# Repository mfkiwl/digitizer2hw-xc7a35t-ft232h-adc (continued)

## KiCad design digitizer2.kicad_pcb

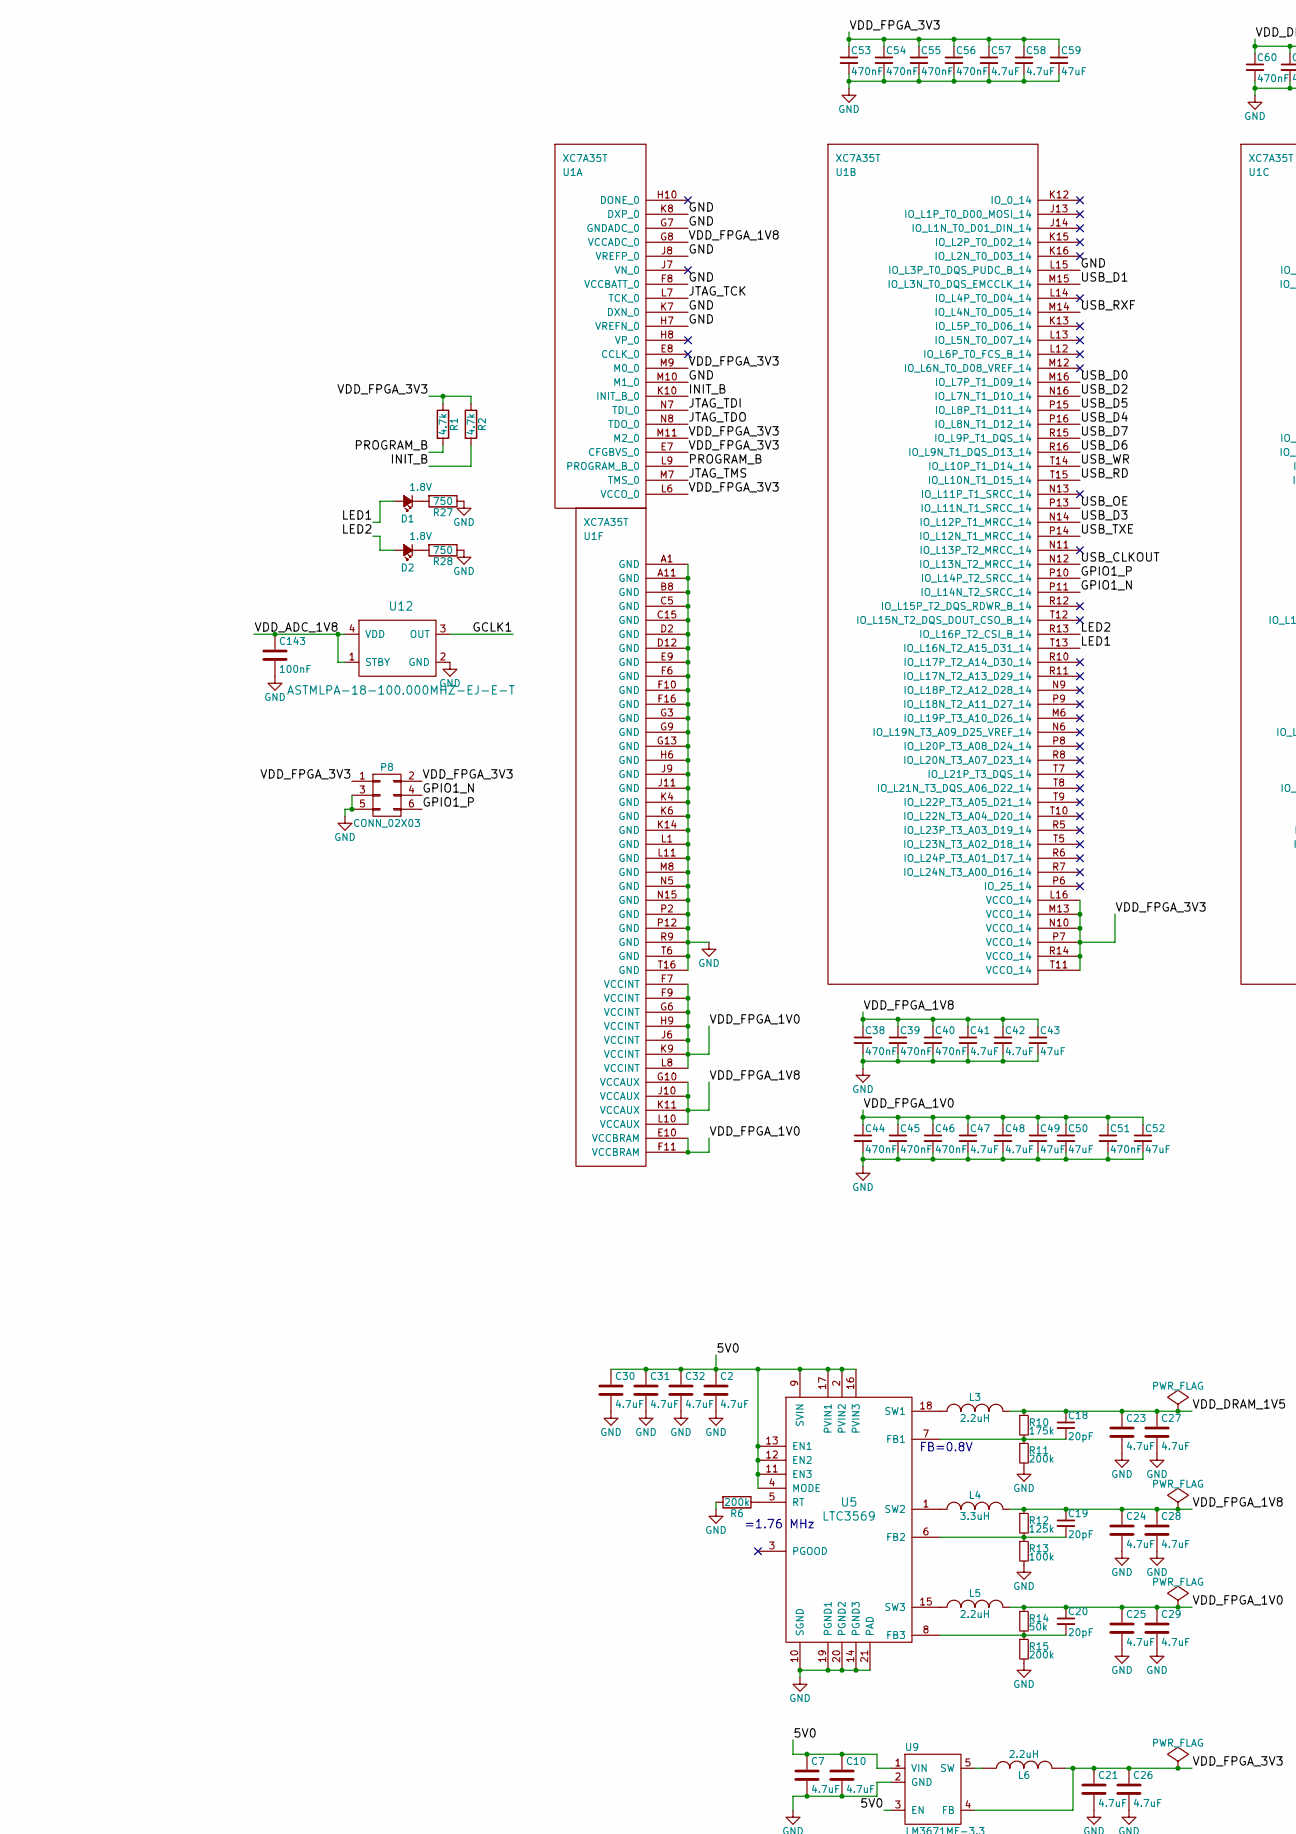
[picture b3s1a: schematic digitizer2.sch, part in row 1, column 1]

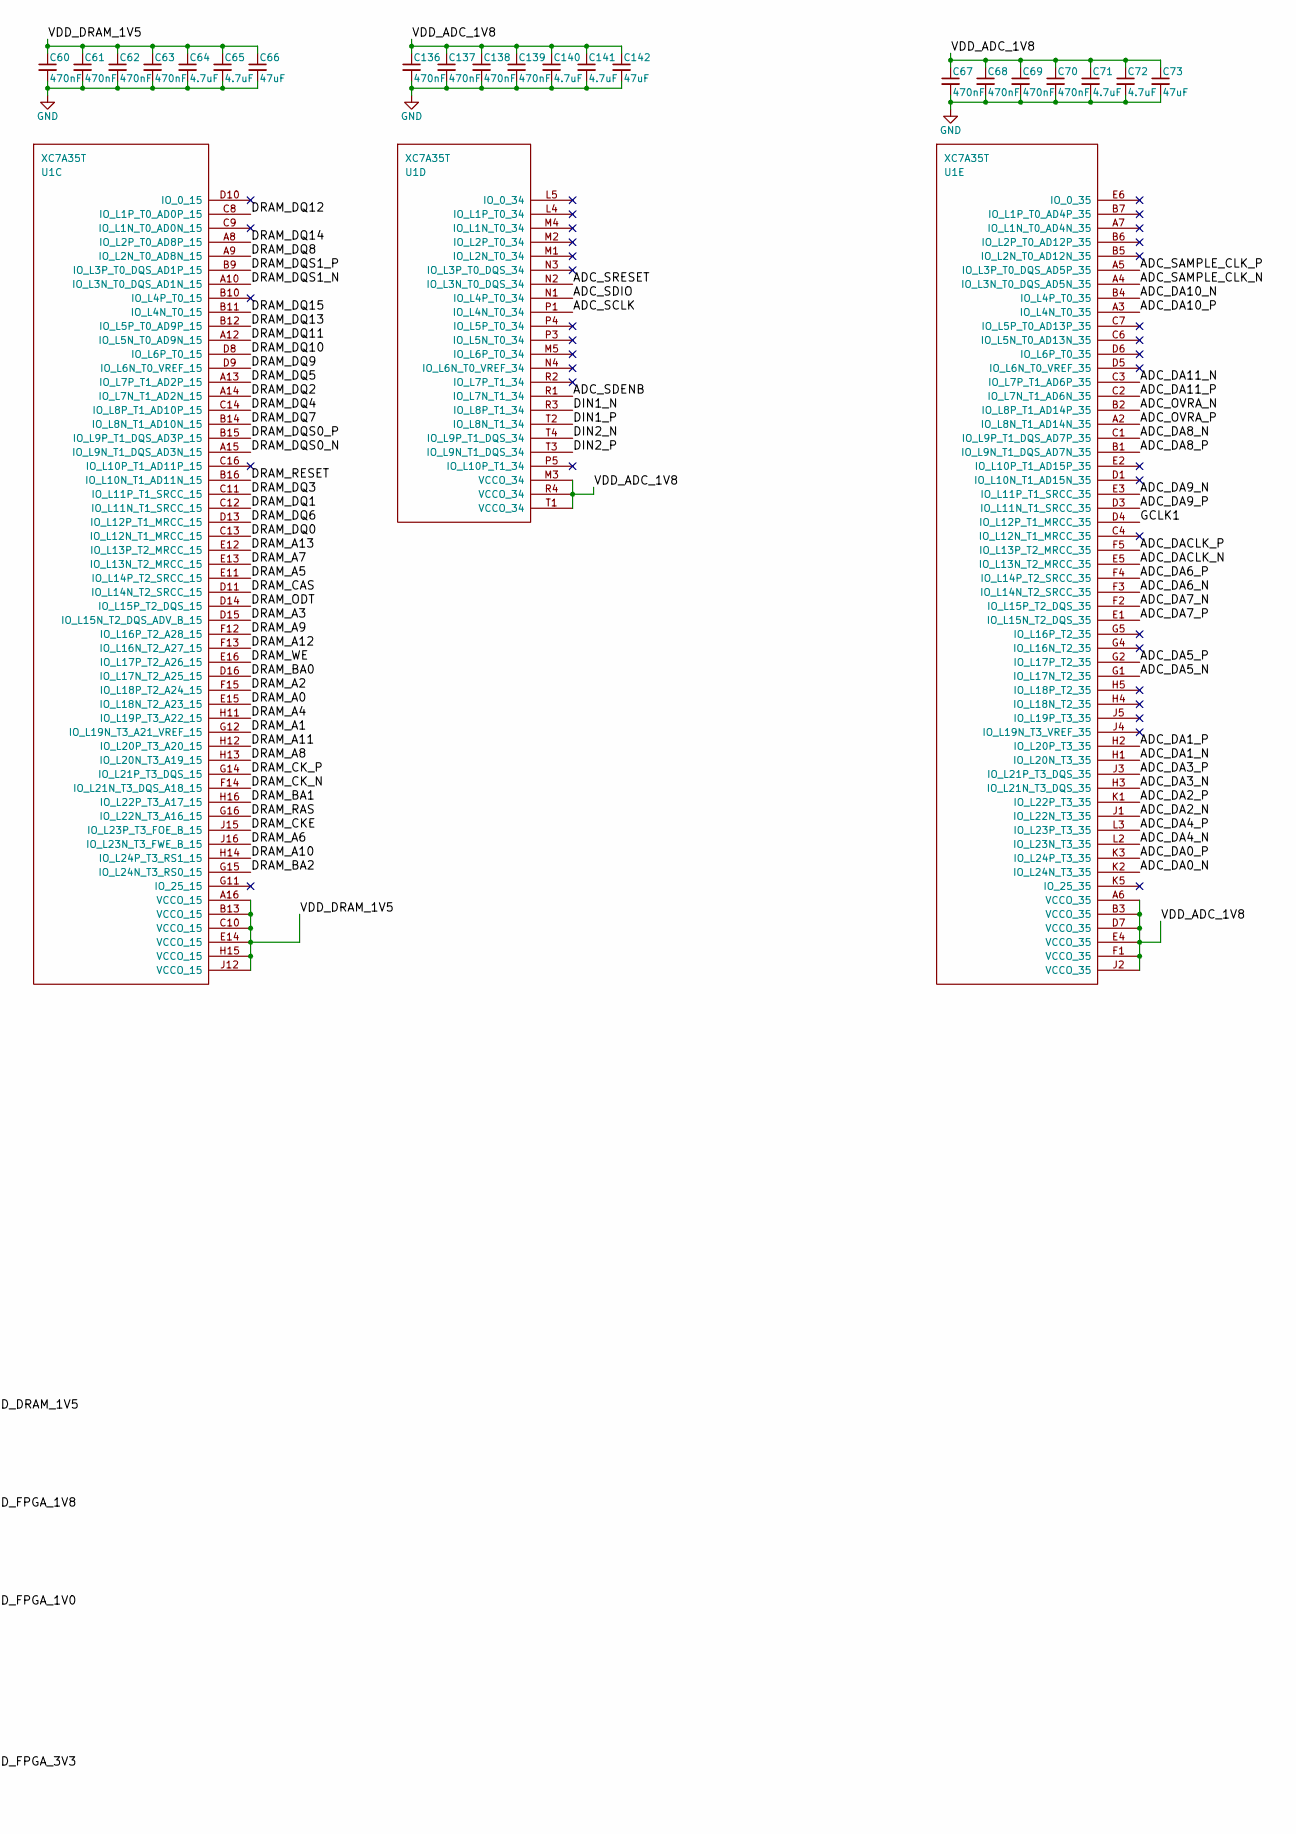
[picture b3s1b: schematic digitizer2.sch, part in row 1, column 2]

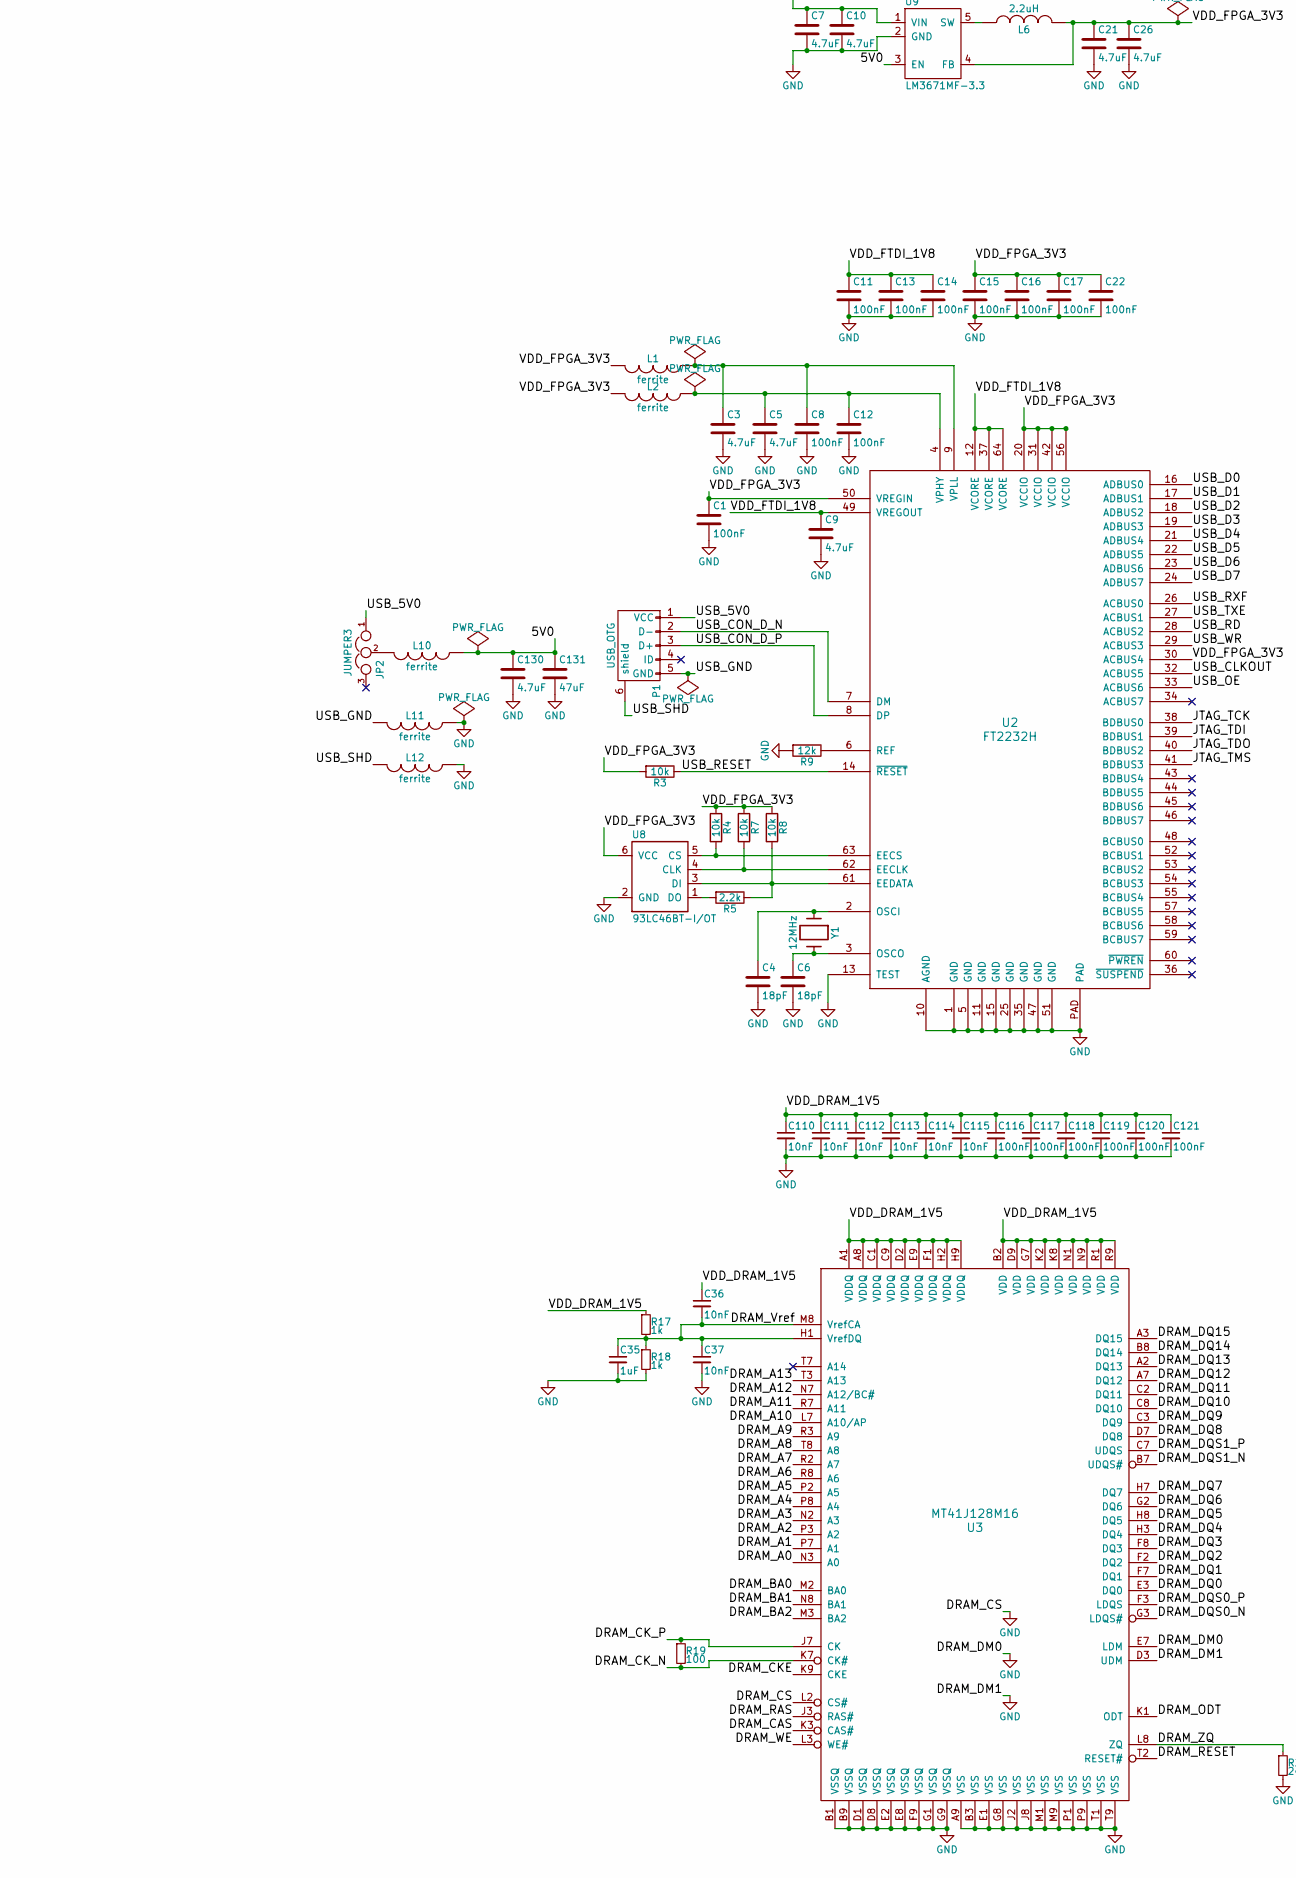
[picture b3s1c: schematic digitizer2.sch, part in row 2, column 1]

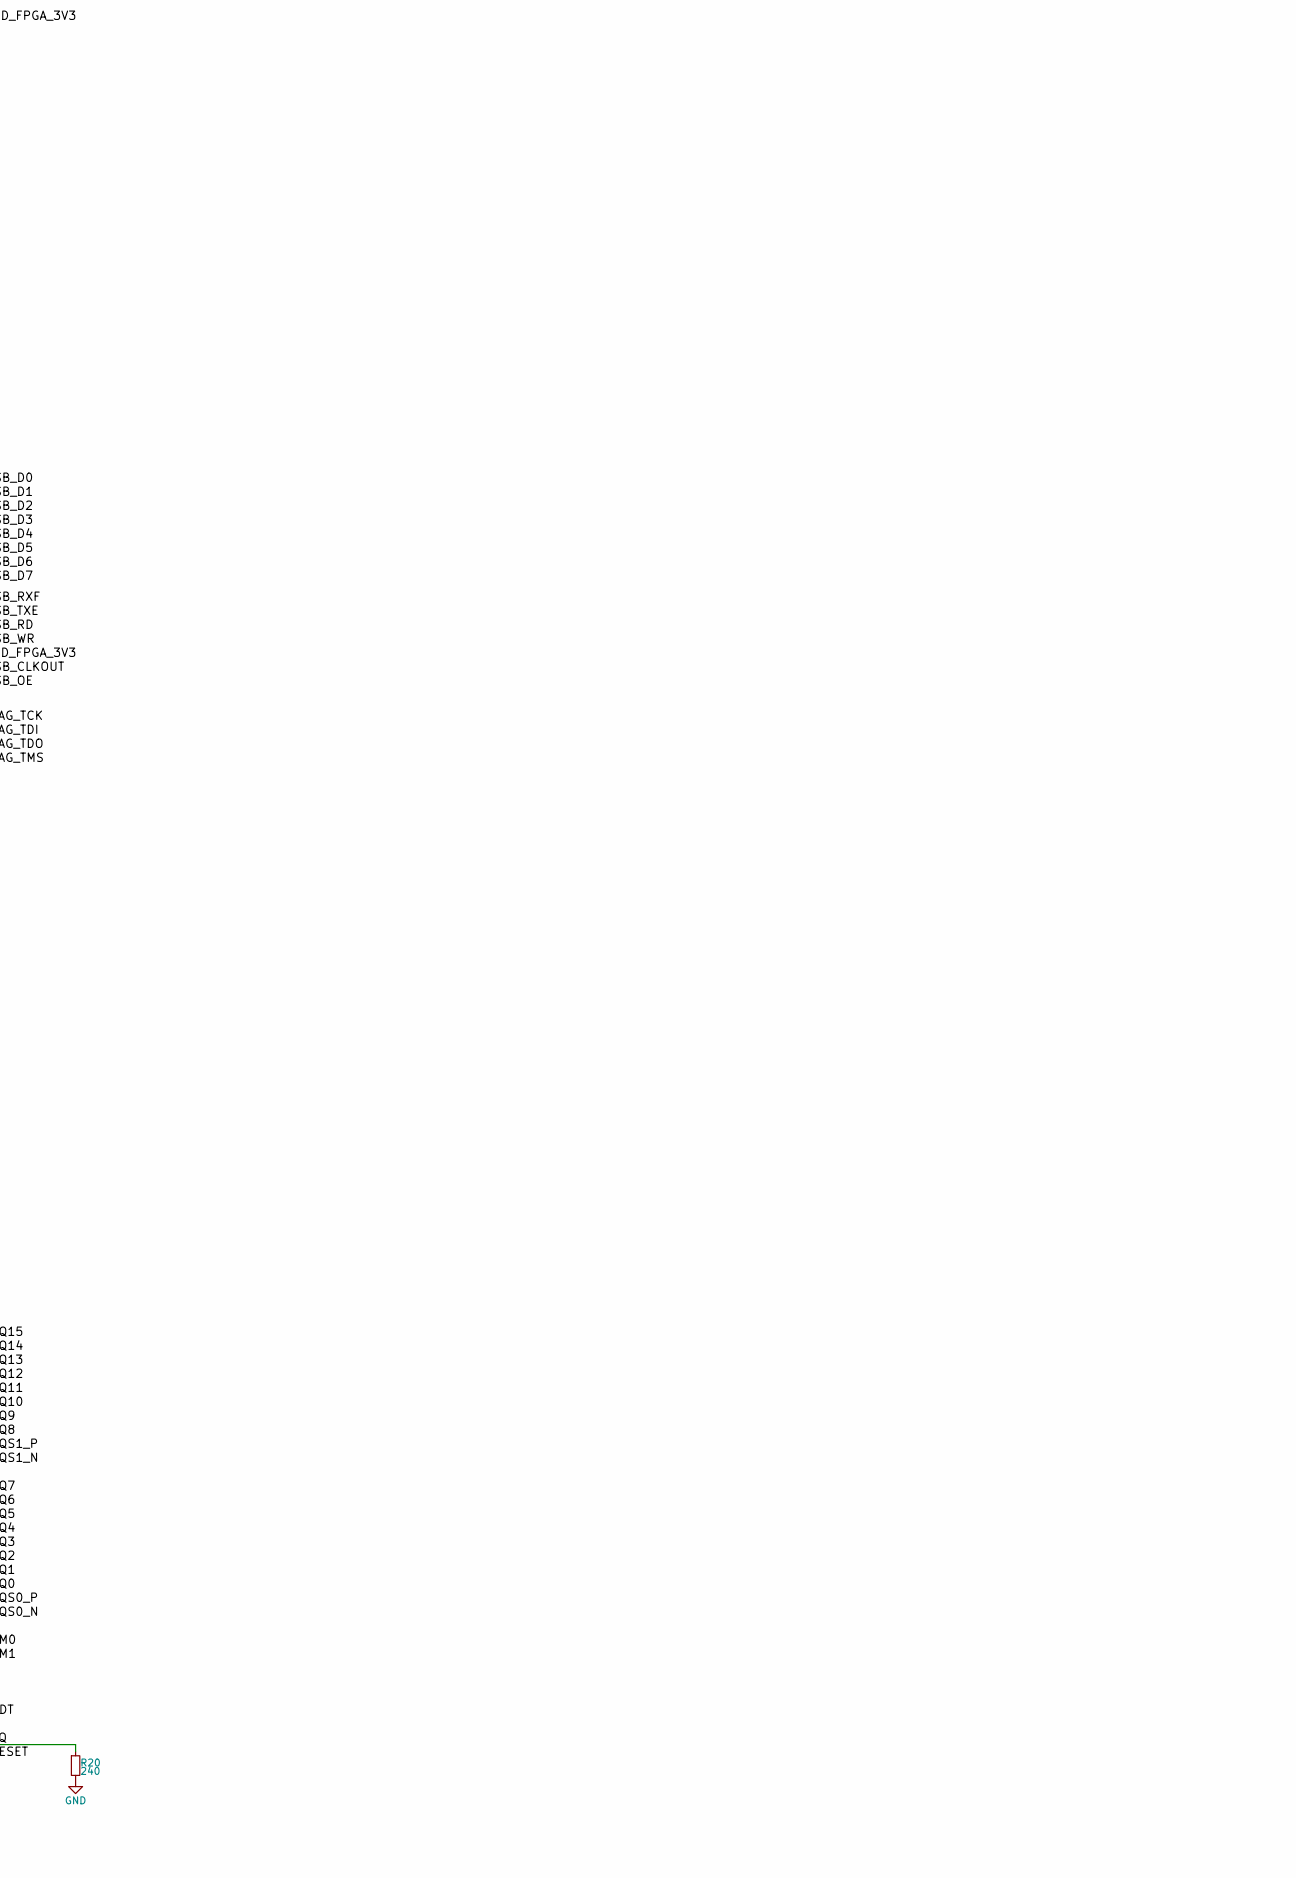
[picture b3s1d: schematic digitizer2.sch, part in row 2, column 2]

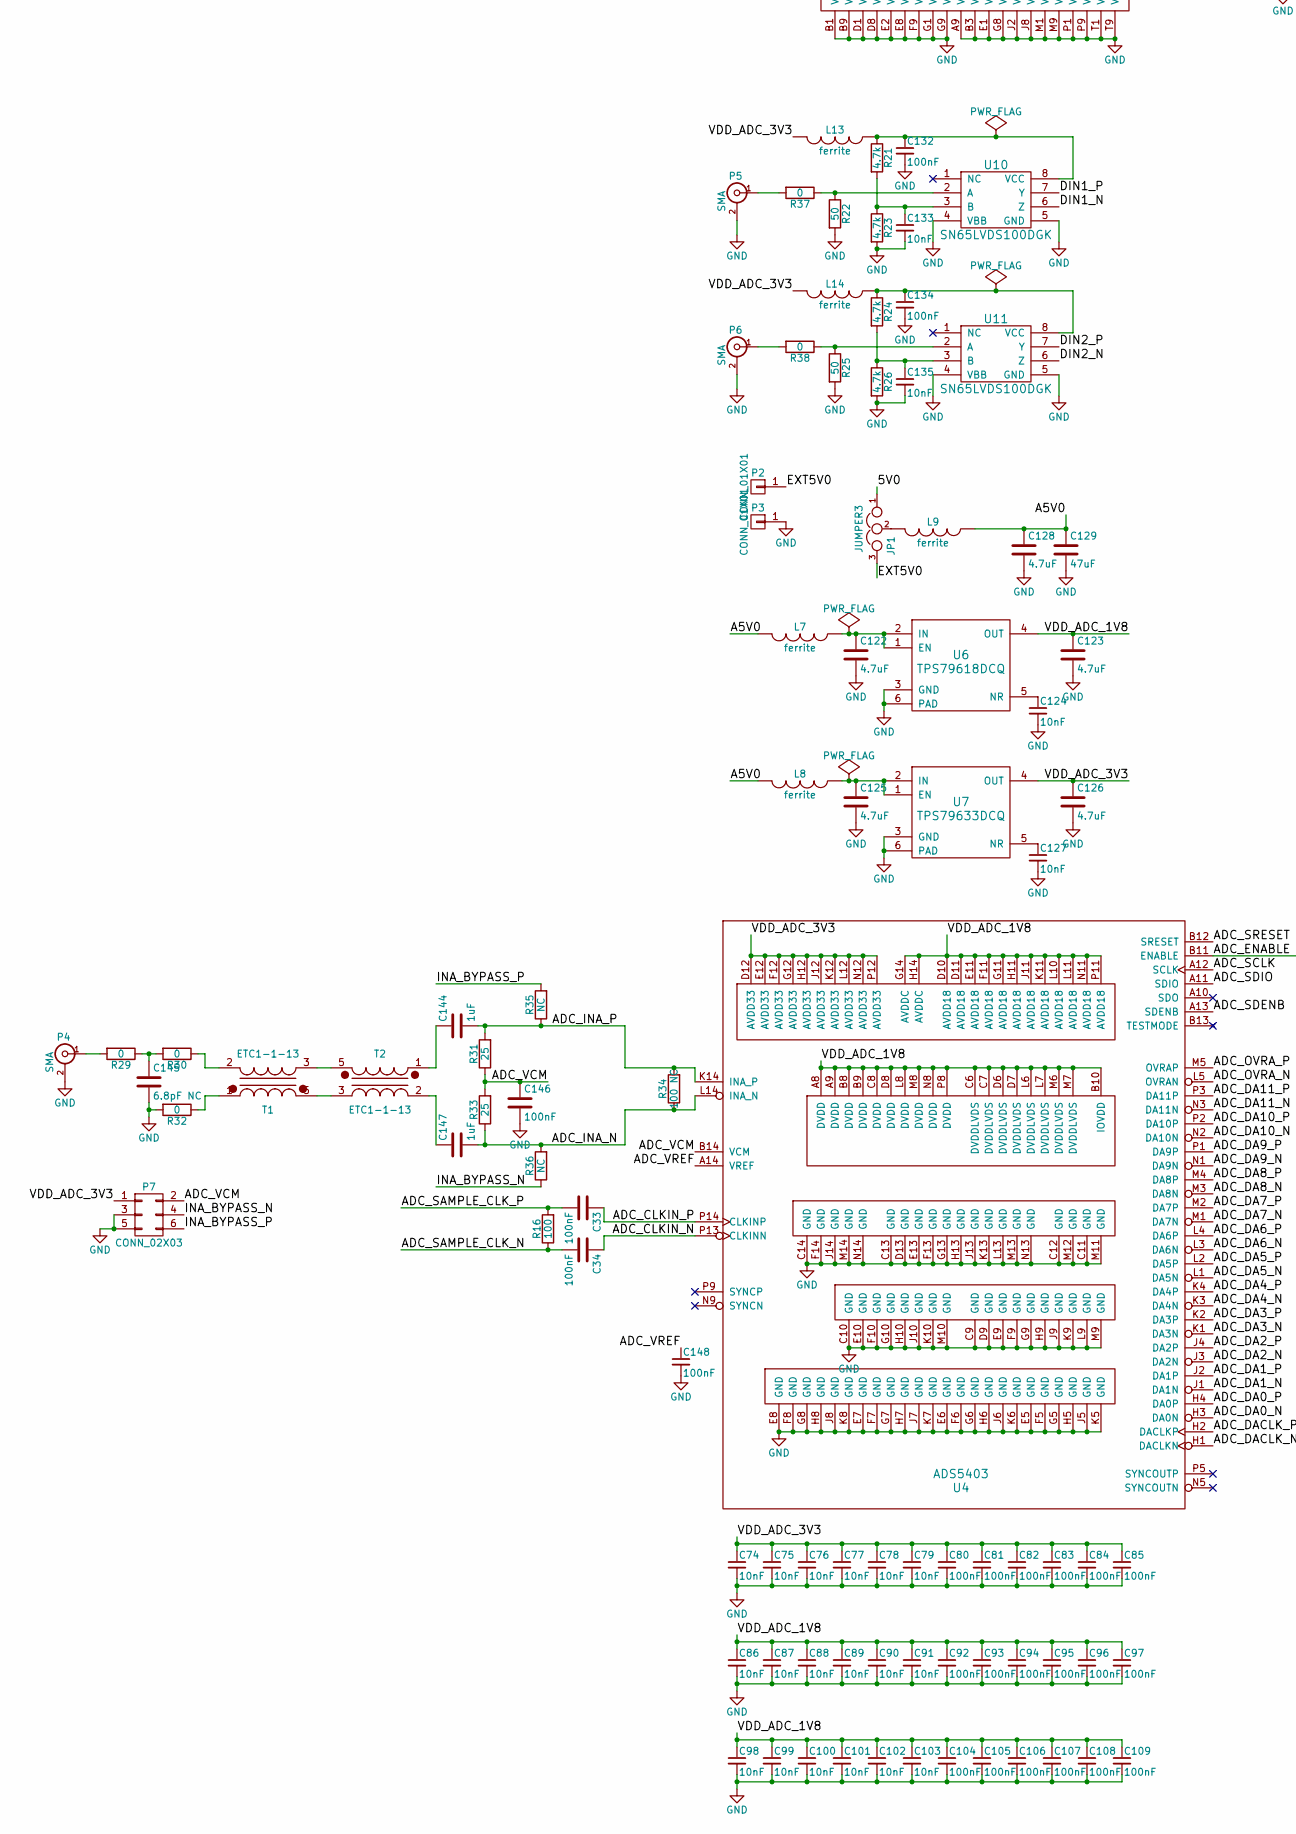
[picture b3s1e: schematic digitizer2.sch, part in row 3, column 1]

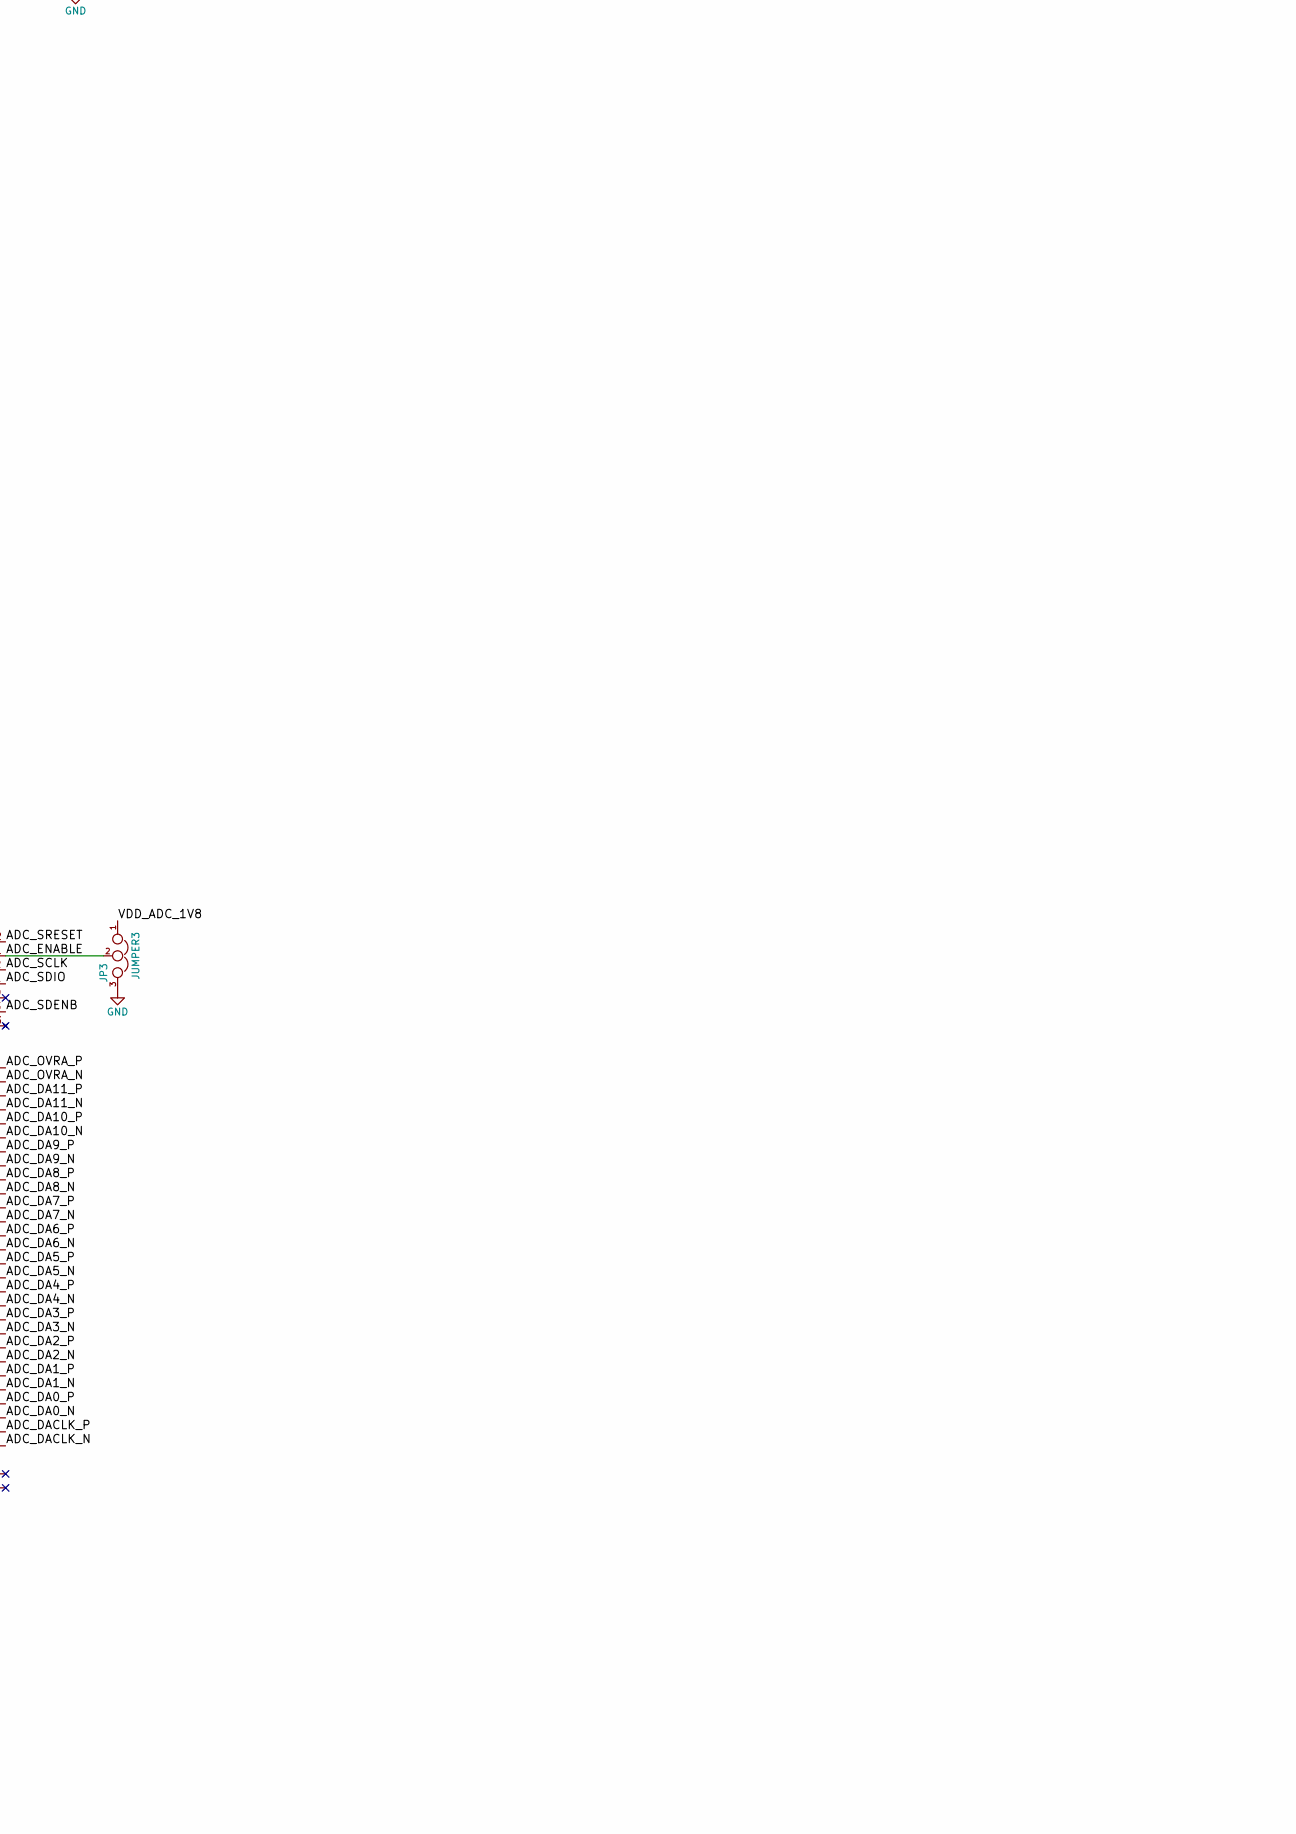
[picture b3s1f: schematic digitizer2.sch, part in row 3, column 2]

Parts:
C1, C8, C11, C12, C13, C14, C15, C16, C17, C22, C33, C34, C80, C81, C82, C83, C84, C85, C92, C93, C94, C95, C96, C97, C104, C105, C106, C107, C108, C109, C116, C117, C118, C119, C120, C121, C132, C134, C143, C146, C148: 100nF; C_0402
C2, C3, C5, C7, C9, C10, C21, C23, C24, C25, C26, C27, C28, C29, C30, C31, C32, C41, C42, C47, C48, C57, C58, C64, C65, C71, C72, C122, C123, C125, C126, C128, C130, C140, C141: 4.7uF; C_0402
C4, C6: 18pF; C_0603
C18, C19, C20: 20pF; C_0603
C35, C144, C147: 1uF; C_0402
C36, C37, C74, C75, C76, C77, C78, C79, C86, C87, C88, C89, C90, C91, C98, C99, C100, C101, C102, C103, C110, C111, C112, C113, C114, C115, C124, C127, C133, C135: 10nF; C_0402
C38, C39, C40, C44, C45, C46, C51, C53, C54, C55, C56, C60, C61, C62, C63, C67, C68, C69, C70, C136, C137, C138, C139: 470nF; C_0402
C43, C49, C50, C52, C59, C66, C73, C129, C131, C142: 47uF; C_0402
C145: 6.8pF NC; C_0603
D1, D2: 1.8V; LED_0603
JP1, JP2, JP3: JUMPER3; Pin_Header_Straight_1x03
L1, L2, L7, L8, L9, L10, L11, L12, L13, L14: ferrite; R_0805
L3, L5, L6: 2.2uH; IHLP-1212BZ-11
L4: 3.3uH; IHLP-1212BZ-11
P1: USB_OTG; USB_Micro-B
P2, P3: CONN_01X01; Banana_Jack_1Pin
P4, P5, P6: SMA; SMA_ANGLE_THT
P7, P8: CONN_02X03; Pin_Header_Angled_2x03
R1, R2, R21, R23, R24, R26: 4.7k; R_0402
R3, R4, R7, R8: 10k; R_0603
R5: 2.2k; R_0603
R6, R11, R15: 200k; R_0603
R9: 12k; R_0603
R10: 175k; R_0603
R12: 125k; R_0603
R13: 100k; R_0603
R14: 50k; R_0603
R16, R19: 100; R_0402
R17, R18: 1k; R_0402
R20: 240; R_0402
R22, R25: 50; R_0402
R27, R28: 750; R_0603
R29, R30, R32: 0; R_0603
R31, R33: 25; R_0402
R34: 100 NC; R_0402
R35, R36: NC; R_0402
R37, R38: 0; R_0402
T1, T2: ETC1-1-13
U1: XC7A35T; BGA-256_pitch1mm_dia0.4mm
U2: FT2232H; QFN-FT2232HQ-64_pitch0.5
U3: MT41J128M16; BGA-96_pitch0.8mm_dia0.35mm
U4: ADS5403; BGA-196_pitch0.8mm_dia0.4mm
U5: LTC3569; UQFN-20-1EP_3x3mm_Pitch0.4mm
U6: TPS79618DCQ; SOT-223-6
U7: TPS79633DCQ; SOT-223-6
U8: 93LC46BT-I/OT; SOT-23-6
U9: LM3671MF-3.3; SOT-23-6
U10, U11: SN65LVDS100DGK; TSSOP-8_3x3mm_Pitch0.65mm
U12: ASTMLPA-18-100.000MHZ-EJ-E-T; ASTMLPA
Y1: 12MHz; Crystal_SMD_5032_2Pads

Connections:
/5V0: C2.1, C7.1, C10.1, C30.1, C31.1, C32.1, C130.1, C131.1, JP1.1, L10.1, U5.2 (PVIN2), U5.4 (MODE), U5.9 (SVIN), U5.11 (EN3), U5.12 (EN2), U5.13 (EN1), U5.16 (PVIN3), U5.17 (PVIN1), U9.1 (VIN), U9.3 (EN)
/A5V0: C128.1, C129.1, L7.2, L8.2, L9.1
/ADC_CLKIN_N: C34.1, U4.P13 (CLKINN)
/ADC_CLKIN_P: C33.1, U4.P14 (CLKINP)
/ADC_DA0_N: U1.K2 (IO_L24N_T3_35), U4.H3 (DA0N)
/ADC_DA0_P: U1.K3 (IO_L24P_T3_35), U4.H4 (DA0P)
/ADC_DA1_N: U1.H1 (IO_L20N_T3_35), U4.J1 (DA1N)
/ADC_DA1_P: U1.H2 (IO_L20P_T3_35), U4.J2 (DA1P)
/ADC_DA2_N: U1.J1 (IO_L22N_T3_35), U4.J3 (DA2N)
/ADC_DA2_P: U1.K1 (IO_L22P_T3_35), U4.J4 (DA2P)
/ADC_DA3_N: U1.H3 (IO_L21N_T3_DQS_35), U4.K1 (DA3N)
/ADC_DA3_P: U1.J3 (IO_L21P_T3_DQS_35), U4.K2 (DA3P)
/ADC_DA4_N: U1.L2 (IO_L23N_T3_35), U4.K3 (DA4N)
/ADC_DA4_P: U1.L3 (IO_L23P_T3_35), U4.K4 (DA4P)
/ADC_DA5_N: U1.G1 (IO_L17N_T2_35), U4.L1 (DA5N)
/ADC_DA5_P: U1.G2 (IO_L17P_T2_35), U4.L2 (DA5P)
/ADC_DA6_N: U1.F3 (IO_L14N_T2_SRCC_35), U4.L3 (DA6N)
/ADC_DA6_P: U1.F4 (IO_L14P_T2_SRCC_35), U4.L4 (DA6P)
/ADC_DA7_N: U1.F2 (IO_L15P_T2_DQS_35), U4.M1 (DA7N)
/ADC_DA7_P: U1.E1 (IO_L15N_T2_DQS_35), U4.M2 (DA7P)
/ADC_DA8_N: U1.C1 (IO_L9P_T1_DQS_AD7P_35), U4.M3 (DA8N)
/ADC_DA8_P: U1.B1 (IO_L9N_T1_DQS_AD7N_35), U4.M4 (DA8P)
/ADC_DA9_N: U1.E3 (IO_L11P_T1_SRCC_35), U4.N1 (DA9N)
/ADC_DA9_P: U1.D3 (IO_L11N_T1_SRCC_35), U4.P1 (DA9P)
/ADC_DA10_N: U1.B4 (IO_L4P_T0_35), U4.N2 (DA10N)
/ADC_DA10_P: U1.A3 (IO_L4N_T0_35), U4.P2 (DA10P)
/ADC_DA11_N: U1.C3 (IO_L7P_T1_AD6P_35), U4.N3 (DA11N)
/ADC_DA11_P: U1.C2 (IO_L7N_T1_AD6N_35), U4.P3 (DA11P)
/ADC_DACLK_N: U1.E5 (IO_L13N_T2_MRCC_35), U4.H1 (DACLKN)
/ADC_DACLK_P: U1.F5 (IO_L13P_T2_MRCC_35), U4.H2 (DACLKP)
/ADC_ENABLE: JP3.2, U4.B11 (ENABLE)
/ADC_INA_N: C147.2, R33.1, R34.1, R36.2, U4.L14 (INA_N)
/ADC_INA_P: C144.2, R31.2, R34.2, R35.1, U4.K14 (INA_P)
/ADC_OVRA_N: U1.B2 (IO_L8P_T1_AD14P_35), U4.L5 (OVRAN)
/ADC_OVRA_P: U1.A2 (IO_L8N_T1_AD14N_35), U4.M5 (OVRAP)
/ADC_SAMPLE_CLK_N: C34.2, R16.1, U1.A4 (IO_L3N_T0_DQS_AD5N_35)
/ADC_SAMPLE_CLK_P: C33.2, R16.2, U1.A5 (IO_L3P_T0_DQS_AD5P_35)
/ADC_SCLK: U1.P1 (IO_L4N_T0_34), U4.A12 (SCLK)
/ADC_SDENB: U1.R1 (IO_L7N_T1_34), U4.A13 (SDENB)
/ADC_SDIO: U1.N1 (IO_L4P_T0_34), U4.A11 (SDIO)
/ADC_SRESET: U1.N2 (IO_L3N_T0_DQS_34), U4.B12 (SRESET)
/ADC_VCM: C146.1, P7.2, R31.1, R33.2, U4.B14 (VCM)
/ADC_VREF: C148.1, U4.A14 (VREF)
/DIN1_N: U1.R3 (IO_L8P_T1_34), U10.6 (Z)
/DIN1_P: U1.T2 (IO_L8N_T1_34), U10.7 (Y)
/DIN2_N: U1.T4 (IO_L9P_T1_DQS_34), U11.6 (Z)
/DIN2_P: U1.T3 (IO_L9N_T1_DQS_34), U11.7 (Y)
/DRAM_A0: U1.E15 (IO_L18N_T2_A23_15), U3.N3 (A0)
/DRAM_A1: U1.G12 (IO_L19N_T3_A21_VREF_15), U3.P7 (A1)
/DRAM_A2: U1.F15 (IO_L18P_T2_A24_15), U3.P3 (A2)
/DRAM_A3: U1.D15 (IO_L15N_T2_DQS_ADV_B_15), U3.N2 (A3)
/DRAM_A4: U1.H11 (IO_L19P_T3_A22_15), U3.P8 (A4)
/DRAM_A5: U1.E11 (IO_L14P_T2_SRCC_15), U3.P2 (A5)
/DRAM_A6: U1.J16 (IO_L23N_T3_FWE_B_15), U3.R8 (A6)
/DRAM_A7: U1.E13 (IO_L13N_T2_MRCC_15), U3.R2 (A7)
/DRAM_A8: U1.H13 (IO_L20N_T3_A19_15), U3.T8 (A8)
/DRAM_A9: U1.F12 (IO_L16P_T2_A28_15), U3.R3 (A9)
/DRAM_A10: U1.H14 (IO_L24P_T3_RS1_15), U3.L7 (A10/AP)
/DRAM_A11: U1.H12 (IO_L20P_T3_A20_15), U3.R7 (A11)
/DRAM_A12: U1.F13 (IO_L16N_T2_A27_15), U3.N7 (A12/BC#)
/DRAM_A13: U1.E12 (IO_L13P_T2_MRCC_15), U3.T3 (A13)
/DRAM_BA0: U1.D16 (IO_L17N_T2_A25_15), U3.M2 (BA0)
/DRAM_BA1: U1.H16 (IO_L22P_T3_A17_15), U3.N8 (BA1)
/DRAM_BA2: U1.G15 (IO_L24N_T3_RS0_15), U3.M3 (BA2)
/DRAM_CAS: U1.D11 (IO_L14N_T2_SRCC_15), U3.K3 (CAS#)
/DRAM_CKE: U1.J15 (IO_L23P_T3_FOE_B_15), U3.K9 (CKE)
/DRAM_CK_N: R19.2, U1.F14 (IO_L21N_T3_DQS_A18_15), U3.K7 (CK#)
/DRAM_CK_P: R19.1, U1.G14 (IO_L21P_T3_DQS_15), U3.J7 (CK)
/DRAM_DQ0: U1.C13 (IO_L12N_T1_MRCC_15), U3.E3 (DQ0)
/DRAM_DQ1: U1.C12 (IO_L11N_T1_SRCC_15), U3.F7 (DQ1)
/DRAM_DQ2: U1.A14 (IO_L7N_T1_AD2N_15), U3.F2 (DQ2)
/DRAM_DQ3: U1.C11 (IO_L11P_T1_SRCC_15), U3.F8 (DQ3)
/DRAM_DQ4: U1.C14 (IO_L8P_T1_AD10P_15), U3.H3 (DQ4)
/DRAM_DQ5: U1.A13 (IO_L7P_T1_AD2P_15), U3.H8 (DQ5)
/DRAM_DQ6: U1.D13 (IO_L12P_T1_MRCC_15), U3.G2 (DQ6)
/DRAM_DQ7: U1.B14 (IO_L8N_T1_AD10N_15), U3.H7 (DQ7)
/DRAM_DQ8: U1.A9 (IO_L2N_T0_AD8N_15), U3.D7 (DQ8)
/DRAM_DQ9: U1.D9 (IO_L6N_T0_VREF_15), U3.C3 (DQ9)
/DRAM_DQ10: U1.D8 (IO_L6P_T0_15), U3.C8 (DQ10)
/DRAM_DQ11: U1.A12 (IO_L5N_T0_AD9N_15), U3.C2 (DQ11)
/DRAM_DQ12: U1.C8 (IO_L1P_T0_AD0P_15), U3.A7 (DQ12)
/DRAM_DQ13: U1.B12 (IO_L5P_T0_AD9P_15), U3.A2 (DQ13)
/DRAM_DQ14: U1.A8 (IO_L2P_T0_AD8P_15), U3.B8 (DQ14)
/DRAM_DQ15: U1.B11 (IO_L4N_T0_15), U3.A3 (DQ15)
/DRAM_DQS0_N: U1.A15 (IO_L9N_T1_DQS_AD3N_15), U3.G3 (LDQS#)
/DRAM_DQS0_P: U1.B15 (IO_L9P_T1_DQS_AD3P_15), U3.F3 (LDQS)
/DRAM_DQS1_N: U1.A10 (IO_L3N_T0_DQS_AD1N_15), U3.B7 (UDQS#)
/DRAM_DQS1_P: U1.B9 (IO_L3P_T0_DQS_AD1P_15), U3.C7 (UDQS)
/DRAM_ODT: U1.D14 (IO_L15P_T2_DQS_15), U3.K1 (ODT)
/DRAM_RAS: U1.G16 (IO_L22N_T3_A16_15), U3.J3 (RAS#)
/DRAM_RESET: U1.B16 (IO_L10N_T1_AD11N_15), U3.T2 (RESET#)
/DRAM_Vref: C35.1, C36.2, C37.1, R17.2, R18.1, U3.H1 (VrefDQ), U3.M8 (VrefCA)
/DRAM_WE: U1.E16 (IO_L17P_T2_A26_15), U3.L3 (WE#)
/DRAM_ZQ: R20.1, U3.L8 (ZQ)
/EXT5V0: JP1.3, P2.1
/GCLK1: U1.D4 (IO_L12P_T1_MRCC_35), U12.3 (OUT)
/GPIO1_N: P8.4, U1.P11 (IO_L14N_T2_SRCC_14)
/GPIO1_P: P8.6, U1.P10 (IO_L14P_T2_SRCC_14)
/INA_BYPASS_N: P7.4, R36.1
/INA_BYPASS_P: P7.6, R35.2
/INIT_B: R2.2, U1.K10 (INIT_B_0)
/JTAG_TCK: U1.L7 (TCK_0), U2.38 (BDBUS0)
/JTAG_TDI: U1.N7 (TDI_0), U2.39 (BDBUS1)
/JTAG_TDO: U1.N8 (TDO_0), U2.40 (BDBUS2)
/JTAG_TMS: U1.M7 (TMS_0), U2.41 (BDBUS3)
/LED1: D1.2 (A), U1.T13 (IO_L16N_T2_A15_D31_14)
/LED2: D2.2 (A), U1.R13 (IO_L16P_T2_CSI_B_14)
/PROGRAM_B: R1.2, U1.L9 (PROGRAM_B_0)
/USB_5V0: JP2.1, P1.1 (VCC)
/USB_CLKOUT: U1.N12 (IO_L13N_T2_MRCC_14), U2.32 (ACBUS5)
/USB_CON_D_N: P1.2 (D-), U2.7 (DM)
/USB_CON_D_P: P1.3 (D+), U2.8 (DP)
/USB_D0: U1.M16 (IO_L7P_T1_D09_14), U2.16 (ADBUS0)
/USB_D1: U1.M15 (IO_L3N_T0_DQS_EMCCLK_14), U2.17 (ADBUS1)
/USB_D2: U1.N16 (IO_L7N_T1_D10_14), U2.18 (ADBUS2)
/USB_D3: U1.N14 (IO_L12P_T1_MRCC_14), U2.19 (ADBUS3)
/USB_D4: U1.P16 (IO_L8N_T1_D12_14), U2.21 (ADBUS4)
/USB_D5: U1.P15 (IO_L8P_T1_D11_14), U2.22 (ADBUS5)
/USB_D6: U1.R16 (IO_L9N_T1_DQS_D13_14), U2.23 (ADBUS6)
/USB_D7: U1.R15 (IO_L9P_T1_DQS_14), U2.24 (ADBUS7)
/USB_GND: L11.2, P1.5 (GND)
/USB_OE: U1.P13 (IO_L11N_T1_SRCC_14), U2.33 (ACBUS6)
/USB_RD: U1.T15 (IO_L10N_T1_D15_14), U2.28 (ACBUS2)
/USB_RESET: R3.1, U2.14 (~RESET)
/USB_RXF: U1.M14 (IO_L4N_T0_D05_14), U2.26 (ACBUS0)
/USB_SHD: L12.2, P1.6 (shield)
/USB_TXE: U1.P14 (IO_L12N_T1_MRCC_14), U2.27 (ACBUS1)
/USB_WR: U1.T14 (IO_L10P_T1_D14_14), U2.29 (ACBUS3)
/VDD_ADC_1V8: C67.1, C68.1, C69.1, C70.1, C71.1, C72.1, C73.1, C86.1, C87.1, C88.1, C89.1, C90.1, C91.1, C92.1, C93.1, C94.1, C95.1, C96.1, C97.1, C98.1, C99.1, C100.1, C101.1, C102.1, C103.1, C104.1, C105.1, C106.1, C107.1, C108.1, C109.1, C123.1, C136.1, C137.1, C138.1, C139.1, C140.1, C141.1, C142.1, C143.1, JP3.1, U1.A6 (VCCO_35), U1.B3 (VCCO_35), U1.D7 (VCCO_35), U1.E4 (VCCO_35), U1.F1 (VCCO_35), U1.J2 (VCCO_35), U1.M3 (VCCO_34), U1.R4 (VCCO_34), U1.T1 (VCCO_34), U4.A8 (DVDD), U4.A9 (DVDD), U4.B8 (DVDD), U4.B9 (DVDD), U4.B10 (IOVDD), U4.C6 (DVDDLVDS), U4.C7 (DVDDLVDS), U4.C8 (DVDD), U4.D6 (DVDDLVDS), U4.D7 (DVDDLVDS), U4.D8 (DVDD), U4.D10 (AVDD18), U4.D11 (AVDD18), U4.E11 (AVDD18), U4.F11 (AVDD18), U4.G11 (AVDD18), U4.G14 (AVDDC), U4.H11 (AVDD18), U4.H14 (AVDDC), U4.J11 (AVDD18), U4.K11 (AVDD18), U4.L6 (DVDDLVDS), U4.L7 (DVDDLVDS), U4.L8 (DVDD), U4.L10 (AVDD18), U4.L11 (AVDD18), U4.M6 (DVDDLVDS), U4.M7 (DVDDLVDS), U4.M8 (DVDD), U4.N8 (DVDD), U4.N11 (AVDD18), U4.P8 (DVDD), U4.P11 (AVDD18), U6.4 (OUT), U12.1 (STBY), U12.4 (VDD)
/VDD_ADC_3V3: C74.1, C75.1, C76.1, C77.1, C78.1, C79.1, C80.1, C81.1, C82.1, C83.1, C84.1, C85.1, C126.1, L13.2, L14.2, P7.1, U4.D12 (AVDD33), U4.E12 (AVDD33), U4.F12 (AVDD33), U4.G12 (AVDD33), U4.H12 (AVDD33), U4.J12 (AVDD33), U4.K12 (AVDD33), U4.L12 (AVDD33), U4.N12 (AVDD33), U4.P12 (AVDD33), U7.4 (OUT)
/VDD_DRAM_1V5: C18.1, C23.1, C27.1, C36.1, C60.1, C61.1, C62.1, C63.1, C64.1, C65.1, C66.1, C110.1, C111.1, C112.1, C113.1, C114.1, C115.1, C116.1, C117.1, C118.1, C119.1, C120.1, C121.1, L3.2, R10.1, R17.1, U1.A16 (VCCO_15), U1.B13 (VCCO_15), U1.C10 (VCCO_15), U1.E14 (VCCO_15), U1.H15 (VCCO_15), U1.J12 (VCCO_15), U3.A1 (VDDQ), U3.A8 (VDDQ), U3.B2 (VDD), U3.C1 (VDDQ), U3.C9 (VDDQ), U3.D2 (VDDQ), U3.D9 (VDD), U3.E9 (VDDQ), U3.F1 (VDDQ), U3.G7 (VDD), U3.H2 (VDDQ), U3.H9 (VDDQ), U3.K2 (VDD), U3.K8 (VDD), U3.N1 (VDD), U3.N9 (VDD), U3.R1 (VDD), U3.R9 (VDD)
/VDD_FPGA_1V0: C20.1, C25.1, C29.1, C44.1, C45.1, C46.1, C47.1, C48.1, C49.1, C50.1, C51.1, C52.1, L5.2, R14.1, U1.E10 (VCCBRAM), U1.F7 (VCCINT), U1.F9 (VCCINT), U1.F11 (VCCBRAM), U1.G6 (VCCINT), U1.H9 (VCCINT), U1.J6 (VCCINT), U1.K9 (VCCINT), U1.L8 (VCCINT)
/VDD_FPGA_1V8: C19.1, C24.1, C28.1, C38.1, C39.1, C40.1, C41.1, C42.1, C43.1, L4.2, R12.1, U1.G8 (VCCADC_0), U1.G10 (VCCAUX), U1.J10 (VCCAUX), U1.K11 (VCCAUX), U1.L10 (VCCAUX)
/VDD_FPGA_3V3: C1.1, C15.1, C16.1, C17.1, C21.1, C22.1, C26.1, C53.1, C54.1, C55.1, C56.1, C57.1, C58.1, C59.1, L1.2, L2.2, L6.2, P8.1, P8.2, R1.1, R2.1, R3.2, R4.1, R7.1, R8.1, U1.E7 (CFGBVS_0), U1.L6 (VCCO_0), U1.L16 (VCCO_14), U1.M9 (M0_0), U1.M11 (M2_0), U1.M13 (VCCO_14), U1.N10 (VCCO_14), U1.P7 (VCCO_14), U1.R14 (VCCO_14), U1.T11 (VCCO_14), U2.20 (VCCIO), U2.30 (ACBUS4), U2.31 (VCCIO), U2.42 (VCCIO), U2.50 (VREGIN), U2.56 (VCCIO), U8.6 (VCC), U9.4 (FB)
/VDD_FTDI_1V8: C9.1, C11.1, C13.1, C14.1, U2.12 (VCORE), U2.37 (VCORE), U2.49 (VREGOUT), U2.64 (VCORE)
GND: C1.2, C2.2, C3.2, C4.2, C5.2, C6.2, C7.2, C8.2, C9.2, C10.2, C11.2, C12.2, C13.2, C14.2, C15.2, C16.2, C17.2, C21.2, C22.2, C23.2, C24.2, C25.2, C26.2, C27.2, C28.2, C29.2, C30.2, C31.2, C32.2, C35.2, C37.2, C38.2, C39.2, C40.2, C41.2, C42.2, C43.2, C44.2, C45.2, C46.2, C47.2, C48.2, C49.2, C50.2, C51.2, C52.2, C53.2, C54.2, C55.2, C56.2, C57.2, C58.2, C59.2, C60.2, C61.2, C62.2, C63.2, C64.2, C65.2, C66.2, C67.2, C68.2, C69.2, C70.2, C71.2, C72.2, C73.2, C74.2, C75.2, C76.2, C77.2, C78.2, C79.2, C80.2, C81.2, C82.2, C83.2, C84.2, C85.2, C86.2, C87.2, C88.2, C89.2, C90.2, C91.2, C92.2, C93.2, C94.2, C95.2, C96.2, C97.2, C98.2, C99.2, C100.2, C101.2, C102.2, C103.2, C104.2, C105.2, C106.2, C107.2, C108.2, C109.2, C110.2, C111.2, C112.2, C113.2, C114.2, C115.2, C116.2, C117.2, C118.2, C119.2, C120.2, C121.2, C122.2, C123.2, C124.2, C125.2, C126.2, C127.2, C128.2, C129.2, C130.2, C131.2, C132.2, C133.2, C134.2, C135.2, C136.2, C137.2, C138.2, C139.2, C140.2, C141.2, C142.2, C143.2, C145.2, C146.2, C148.2, JP3.3, L11.1, L12.1, P3.1, P4.2 (Ext), P5.2 (Ext), P6.2 (Ext), P7.3, P7.5, P8.3, P8.5, R6.2, R9.2, R11.2, R13.2, R15.2, R18.2, R20.2, R22.2, R23.2, R25.2, R26.2, R27.1, R28.1, R32.2, U1.A1 (GND), U1.A11 (GND), U1.B8 (GND), U1.C5 (GND), U1.C15 (GND), U1.D2 (GND), U1.D12 (GND), U1.E9 (GND), U1.F6 (GND), U1.F8 (VCCBATT_0), U1.F10 (GND), U1.F16 (GND), U1.G3 (GND), U1.G7 (GNDADC_0)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
unnamed: C3.1, C8.1, L1.1, U2.9 (VPLL)
unnamed: C4.1, U2.2 (OSCI), Y1.1
unnamed: C6.1, U2.3 (OSCO), Y1.2
unnamed: C5.1, C12.1, L2.1, U2.4 (VPHY)
unnamed: C18.2, R10.2, R11.1, U5.7 (FB1)
unnamed: C19.2, R12.2, R13.1, U5.6 (FB2)
unnamed: C20.2, R14.2, R15.1, U5.8 (FB3)
unnamed: C122.1, L7.1, U6.1 (EN), U6.2 (IN)
unnamed: C124.1, U6.5 (NR)
unnamed: C125.1, L8.1, U7.1 (EN), U7.2 (IN)
unnamed: C127.1, U7.5 (NR)
unnamed: C132.1, L13.1, R21.1, U10.8 (VCC)
unnamed: C133.1, R21.2, R23.1, U10.3 (B)
unnamed: C134.1, L14.1, R24.1, U11.8 (VCC)
unnamed: C135.1, R24.2, R26.1, U11.3 (B)
unnamed: C144.1, T2.1 (PA)
unnamed: C145.1, R29.1, R30.2
unnamed: C147.1, T2.2 (PB)
unnamed: D1.1 (K), R27.2
unnamed: D2.1 (K), R28.2
unnamed: JP1.2, L9.2
unnamed: JP2.2, L10.2
unnamed: L3.1, U5.18 (SW1)
unnamed: L4.1, U5.1 (SW2)
unnamed: L5.1, U5.15 (SW3)
unnamed: L6.1, U9.5 (SW)
unnamed: P4.1 (In), R29.2
unnamed: P5.1 (In), R37.2
unnamed: P6.1 (In), R38.2
unnamed: R4.2, U2.63 (EECS), U8.5 (CS)
unnamed: R5.1, R8.2, U2.61 (EEDATA), U8.3 (DI)
unnamed: R5.2, U8.1 (DO)
unnamed: R6.1, U5.5 (RT)
unnamed: R7.2, U2.62 (EECLK), U8.4 (CLK)
unnamed: R9.1, U2.6 (REF)
unnamed: R22.1, R37.1, U10.2 (A)
unnamed: R25.1, R38.1, U11.2 (A)
unnamed: R30.1, T1.2 (PB)
unnamed: R32.1, T1.1 (PA)
unnamed: T1.3 (SB), T2.5 (SA)
unnamed: T1.5 (SA), T2.3 (SB)

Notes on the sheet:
=1.76 MHz
FB=0.8V
